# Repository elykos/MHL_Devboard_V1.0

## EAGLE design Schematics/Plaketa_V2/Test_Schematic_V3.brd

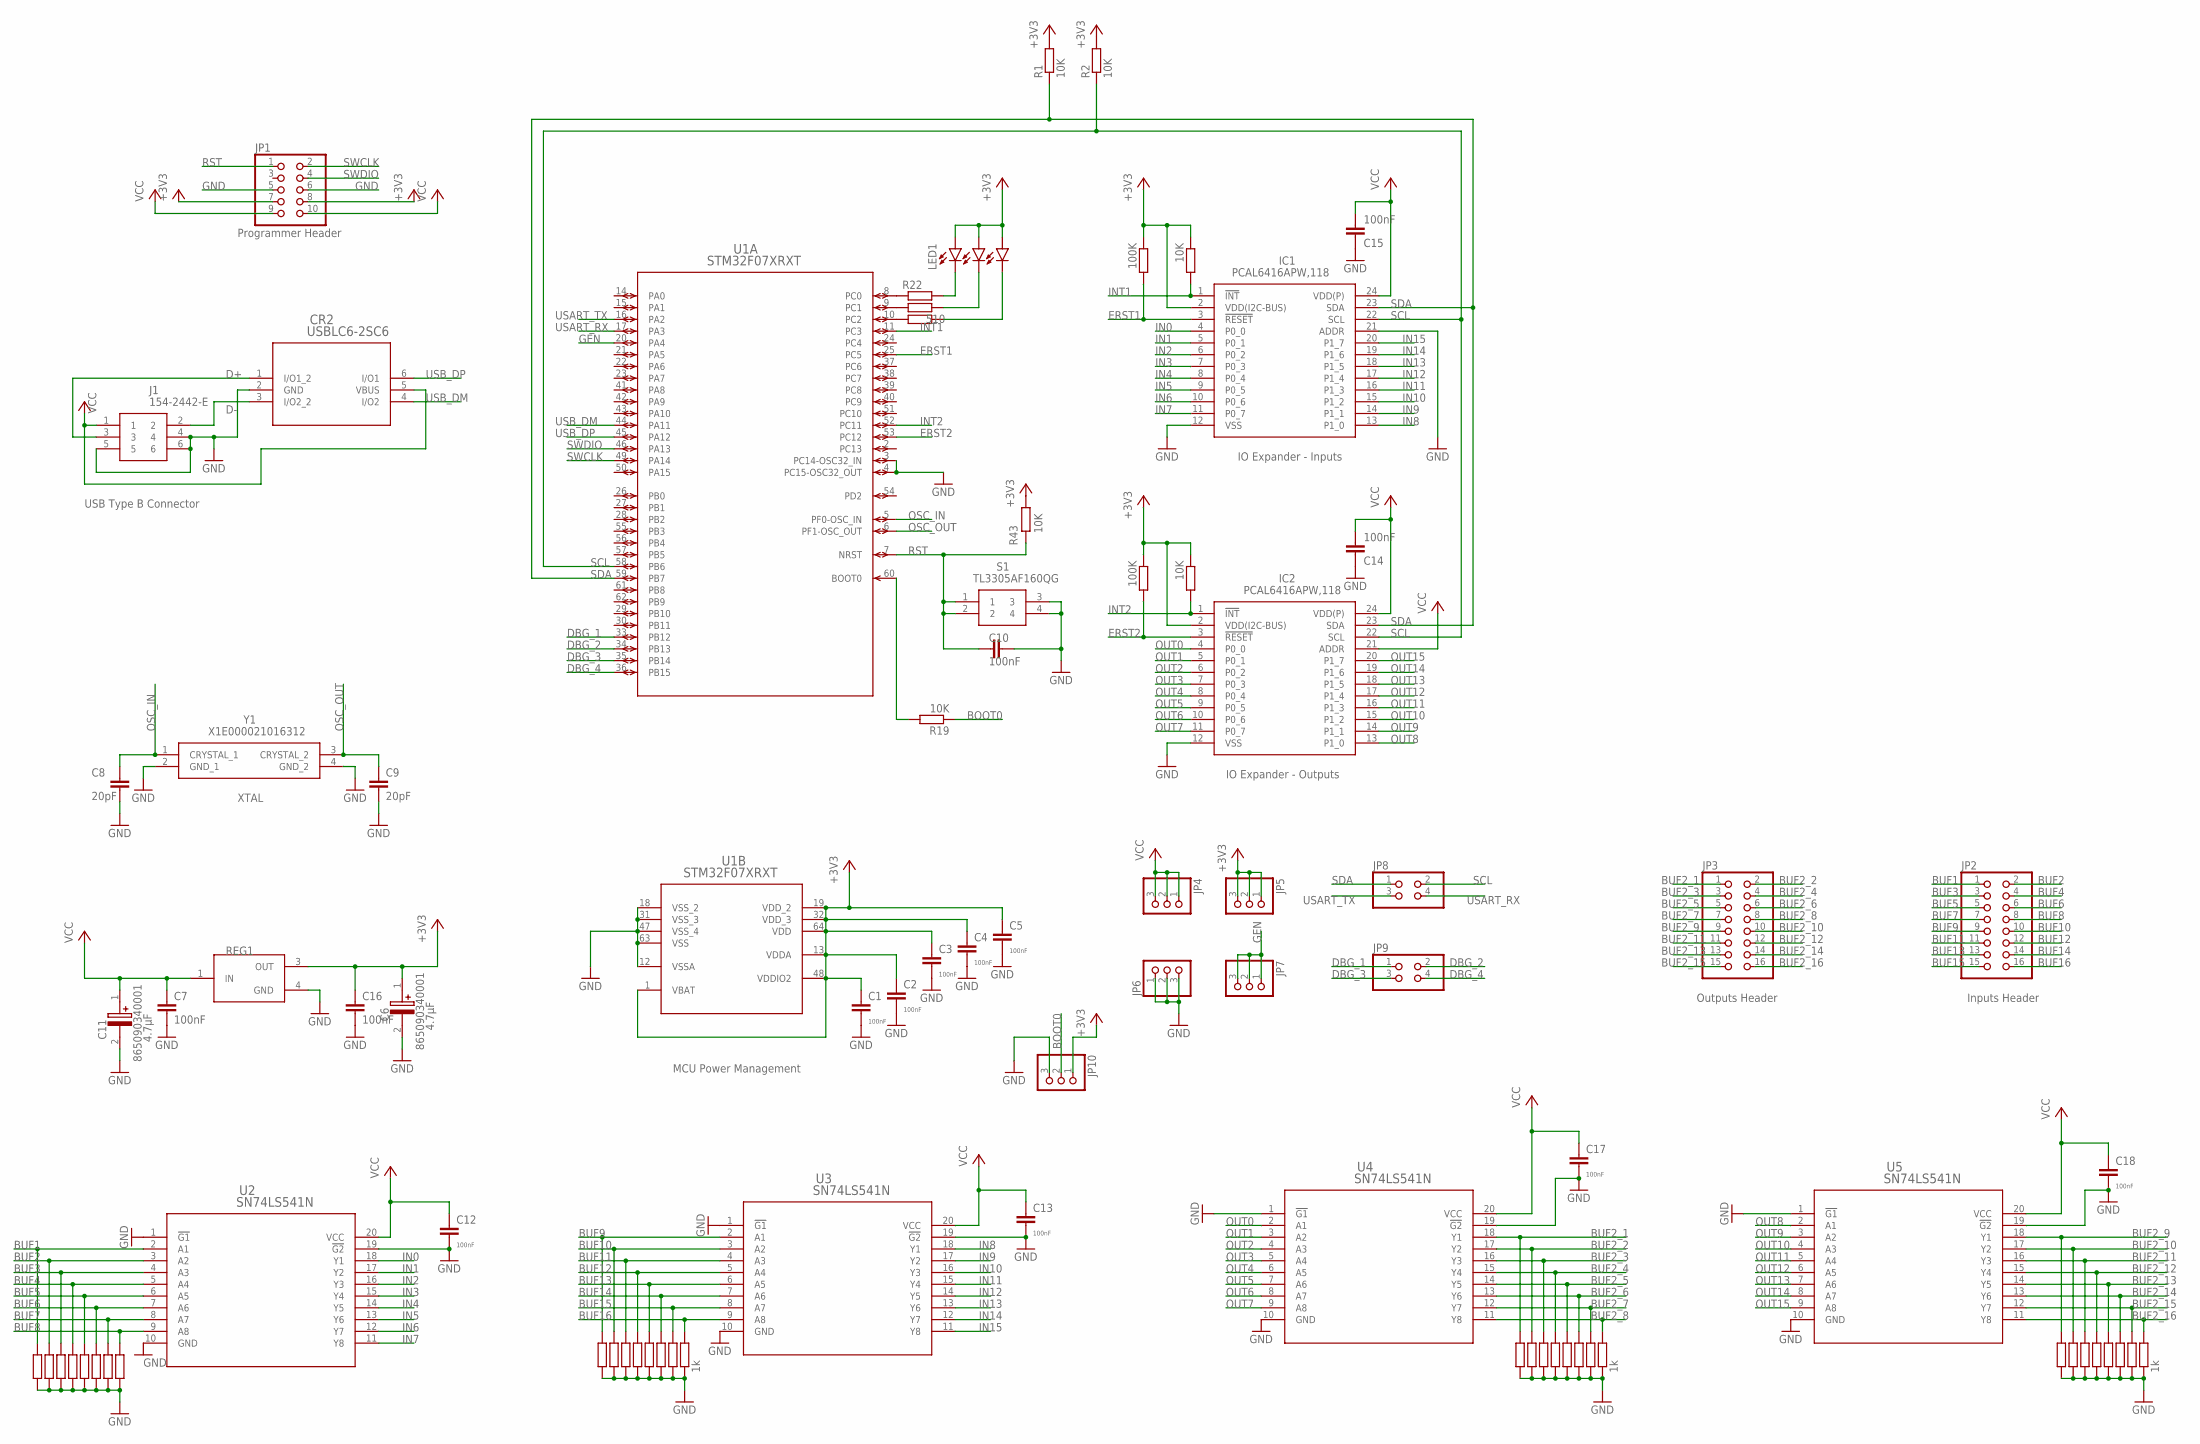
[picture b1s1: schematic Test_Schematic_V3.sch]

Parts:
C1, C2, C3, C4, C5, C7, C10, C12, C13, C14, C15, C16, C17, C18: 100nF; C1206
C6, C11: 865090340001; CAPAE430X550N
C8, C9: 20pF; C0805K
CR2: USBLC6-2SC6; SOT23-6L
IC1, IC2: PCAL6416APW,118; SOP65P640X110-24N
J1: 154-2442-E; 1542442E
JP1: PINHD-2X5; 2X05
JP2, JP3: PINHD-2X8; 2X08
JP4, JP5, JP6, JP7, JP10: PINHD-1X3; 1X03
JP8, JP9: PINHD-2X2; 2X02
LED1, LED2, LED3: LEDCHIP-LED0805; CHIP-LED0805
R1, R2, R19, R25, R26: 10K; R2010
R11, R12, R13, R14, R15, R16, R17, R22, R23, R28, R29, R30, R31, R32, R33, R34, R45, R46, R47, R48, R49, R50, R51, R53, R54, R55, R56, R57, R58, R59: R-EU_R0805; R0805
R18, R27, R44, R52: 1k; R0805
R20, R21: 100K; R2010
R24: 510; R0805
R43: 10K; R0805
REG1: LF33ABDT; DPAK
S1: TL3305AF160QG
U1: STM32F07XRXT; LQFP64-10X10MM
U2, U3, U4, U5: SN74LS541N; N20
Y1: X1E000021016312; TSX-3225_2

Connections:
+3V3: C1.1, C2.1, C3.1, C4.1, C5.1, C6.1 (+), C16.1, IC1.2 (VDD(I2C-BUS)), IC2.2 (VDD(I2C-BUS)), JP1.7, JP1.8, JP5.1, JP5.2, JP5.3, JP10.1, LED1.A, LED2.A, LED3.A, R1.2, R2.2, R20.1, R21.1, R25.1, R26.1, R43.1, REG1.3 (OUT), U1.1 (VBAT), U1.13 (VDDA), U1.19 (VDD_2), U1.32 (VDD_3), U1.48 (VDDIO2), U1.64 (VDD)
BOOT0: JP10.2, R19.1
BUF1: JP2.1, R11.2, U2.2 (A1)
BUF2: JP2.2, R12.2, U2.3 (A2)
BUF2_1: JP3.1, R51.2, U4.18 (Y1)
BUF2_2: JP3.2, R50.2, U4.17 (Y2)
BUF2_3: JP3.3, R49.2, U4.16 (Y3)
BUF2_4: JP3.4, R48.2, U4.15 (Y4)
BUF2_5: JP3.5, R47.2, U4.14 (Y5)
BUF2_6: JP3.6, R46.1, U4.13 (Y6)
BUF2_7: JP3.7, R45.2, U4.12 (Y7)
BUF2_8: JP3.8, R44.2, U4.11 (Y8)
BUF2_9: JP3.9, R59.2, U5.18 (Y1)
BUF2_10: JP3.10, R58.2, U5.17 (Y2)
BUF2_11: JP3.11, R57.2, U5.16 (Y3)
BUF2_12: JP3.12, R56.2, U5.15 (Y4)
BUF2_13: JP3.13, R55.2, U5.14 (Y5)
BUF2_14: JP3.14, R54.1, U5.13 (Y6)
BUF2_15: JP3.15, R53.2, U5.12 (Y7)
BUF2_16: JP3.16, R52.2, U5.11 (Y8)
BUF3: JP2.3, R13.2, U2.4 (A3)
BUF4: JP2.4, R14.2, U2.5 (A4)
BUF5: JP2.5, R15.2, U2.6 (A5)
BUF6: JP2.6, R16.2, U2.7 (A6)
BUF7: JP2.7, R17.2, U2.8 (A7)
BUF8: JP2.8, R18.2, U2.9 (A8)
BUF9: JP2.9, R34.2, U3.2 (A1)
BUF10: JP2.10, R33.2, U3.3 (A2)
BUF11: JP2.11, R32.2, U3.4 (A3)
BUF12: JP2.12, R31.2, U3.5 (A4)
BUF13: JP2.13, R30.2, U3.6 (A5)
BUF14: JP2.14, R29.1, U3.7 (A6)
BUF15: JP2.15, R28.2, U3.8 (A7)
BUF16: JP2.16, R27.2, U3.9 (A8)
D+: CR2.1 (I/O1_2), J1.3
D-: CR2.3 (I/O2_2), J1.2
DBG_1: JP9.1, U1.33 (PB12)
DBG_2: JP9.2, U1.34 (PB13)
DBG_3: JP9.3, U1.35 (PB14)
DBG_4: JP9.4, U1.36 (PB15)
ERST1: IC1.3 (!RESET), R20.2, U1.25 (PC5)
ERST2: IC2.3 (!RESET), R21.2, U1.53 (PC12)
GEN: JP7.1, JP7.2, JP7.3, U1.20 (PA4)
GND: C1.2, C2.2, C3.2, C4.2, C5.2, C6.2 (-), C7.2, C8.2, C9.2, C10.2, C11.2 (-), C12.2, C13.2, C14.1, C15.1, C16.2, C17.2, C18.2, CR2.2 (GND), IC1.12 (VSS), IC1.21 (ADDR), IC2.12 (VSS), J1.4, J1.5, J1.6, JP1.5, JP1.6, JP6.1, JP6.2, JP6.3, JP10.3, R11.1, R12.1, R13.1, R14.1, R15.1, R16.1, R17.1, R18.1, R27.1, R28.1, R29.2, R30.1, R31.1, R32.1, R33.1, R34.1, R44.1, R45.1, R46.2, R47.1, R48.1, R49.1, R50.1, R51.1, R52.1, R53.1, R54.2, R55.1, R56.1, R57.1, R58.1, R59.1, REG1.4 (GND), S1.3, S1.4, U1.3 (PC14-OSC32_IN), U1.4 (PC15-OSC32_OUT), U1.12 (VSSA), U1.18 (VSS_2), U1.31 (VSS_3), U1.47 (VSS_4), U1.63 (VSS), U2.1 (!G1), U2.10 (GND), U2.19 (!G2), U3.1 (!G1), U3.10 (GND), U3.19 (!G2), U4.1 (!G1), U4.10 (GND), U4.19 (!G2), U5.1 (!G1), U5.10 (GND), U5.19 (!G2), Y1.2 (GND_1), Y1.4 (GND_2)
IN0: IC1.4 (P0_0), U2.18 (Y1)
IN1: IC1.5 (P0_1), U2.17 (Y2)
IN2: IC1.6 (P0_2), U2.16 (Y3)
IN3: IC1.7 (P0_3), U2.15 (Y4)
IN4: IC1.8 (P0_4), U2.14 (Y5)
IN5: IC1.9 (P0_5), U2.13 (Y6)
IN6: IC1.10 (P0_6), U2.12 (Y7)
IN7: IC1.11 (P0_7), U2.11 (Y8)
IN8: IC1.13 (P1_0), U3.18 (Y1)
IN9: IC1.14 (P1_1), U3.17 (Y2)
IN10: IC1.15 (P1_2), U3.16 (Y3)
IN11: IC1.16 (P1_3), U3.15 (Y4)
IN12: IC1.17 (P1_4), U3.14 (Y5)
IN13: IC1.18 (P1_5), U3.13 (Y6)
IN14: IC1.19 (P1_6), U3.12 (Y7)
IN15: IC1.20 (P1_7), U3.11 (Y8)
INT1: IC1.1 (!INT), R26.2, U1.11 (PC3)
INT2: IC2.1 (!INT), R25.2, U1.52 (PC11)
unnamed: R22.1, U1.8 (PC0)
unnamed: R19.2, U1.60 (BOOT0)
unnamed: LED1.C, R22.2
unnamed: R23.1, U1.9 (PC1)
unnamed: LED2.C, R23.2
unnamed: LED3.C, R24.2
unnamed: R24.1, U1.10 (PC2)
OSC_IN: C8.1, U1.5 (PF0-OSC_IN), Y1.1 (CRYSTAL_1)
OSC_OUT: C9.1, U1.6 (PF1-OSC_OUT), Y1.3 (CRYSTAL_2)
OUT0: IC2.4 (P0_0), U4.2 (A1)
OUT1: IC2.5 (P0_1), U4.3 (A2)
OUT2: IC2.6 (P0_2), U4.4 (A3)
OUT3: IC2.7 (P0_3), U4.5 (A4)
OUT4: IC2.8 (P0_4), U4.6 (A5)
OUT5: IC2.9 (P0_5), U4.7 (A6)
OUT6: IC2.10 (P0_6), U4.8 (A7)
OUT7: IC2.11 (P0_7), U4.9 (A8)
OUT8: IC2.13 (P1_0), U5.2 (A1)
OUT9: IC2.14 (P1_1), U5.3 (A2)
OUT10: IC2.15 (P1_2), U5.4 (A3)
OUT11: IC2.16 (P1_3), U5.5 (A4)
OUT12: IC2.17 (P1_4), U5.6 (A5)
OUT13: IC2.18 (P1_5), U5.7 (A6)
OUT14: IC2.19 (P1_6), U5.8 (A7)
OUT15: IC2.20 (P1_7), U5.9 (A8)
RST: C10.1, JP1.1, R43.2, S1.1, S1.2, U1.7 (NRST)
SCL: IC1.22 (SCL), IC2.22 (SCL), JP8.2, R2.1, U1.58 (PB6)
SDA: IC1.23 (SDA), IC2.23 (SDA), JP8.1, R1.1, U1.59 (PB7)
SWCLK: JP1.2, U1.49 (PA14)
SWDIO: JP1.4, U1.46 (PA13)
USART_RX: JP8.4, U1.17 (PA3)
USART_TX: JP8.3, U1.16 (PA2)
USB_DM: CR2.4 (I/O2), U1.44 (PA11)
USB_DP: CR2.6 (I/O1), U1.45 (PA12)
VCC: C7.1, C11.1 (+), C12.1, C13.1, C14.2, C15.2, C17.1, C18.1, CR2.5 (VBUS), IC1.24 (VDD(P)), IC2.21 (ADDR), IC2.24 (VDD(P)), J1.1, JP1.9, JP1.10, JP4.1, JP4.2, JP4.3, REG1.1 (IN), U2.20 (VCC), U3.20 (VCC), U4.20 (VCC), U5.20 (VCC)

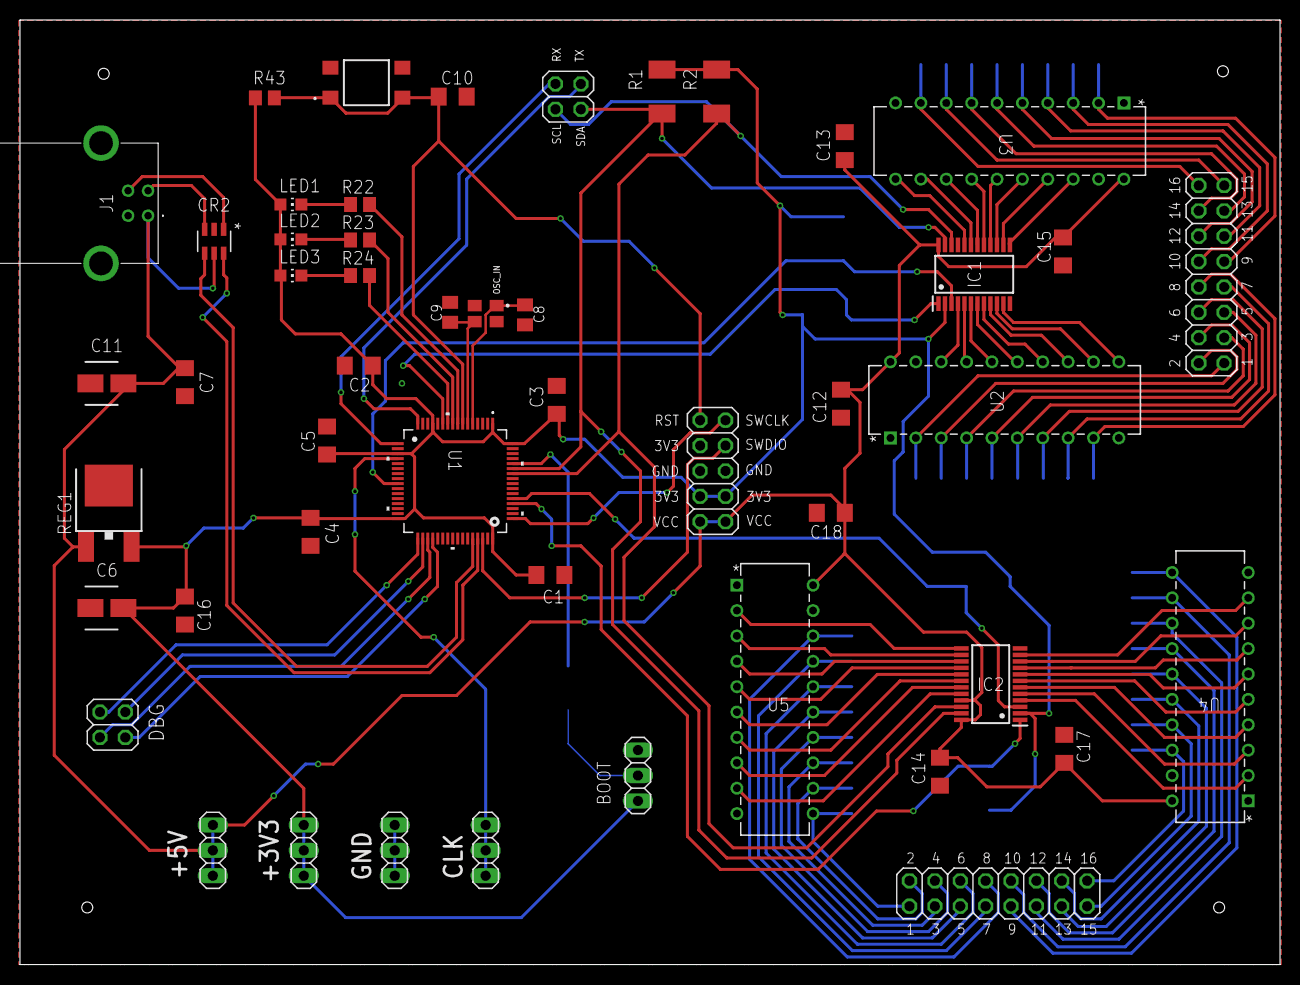
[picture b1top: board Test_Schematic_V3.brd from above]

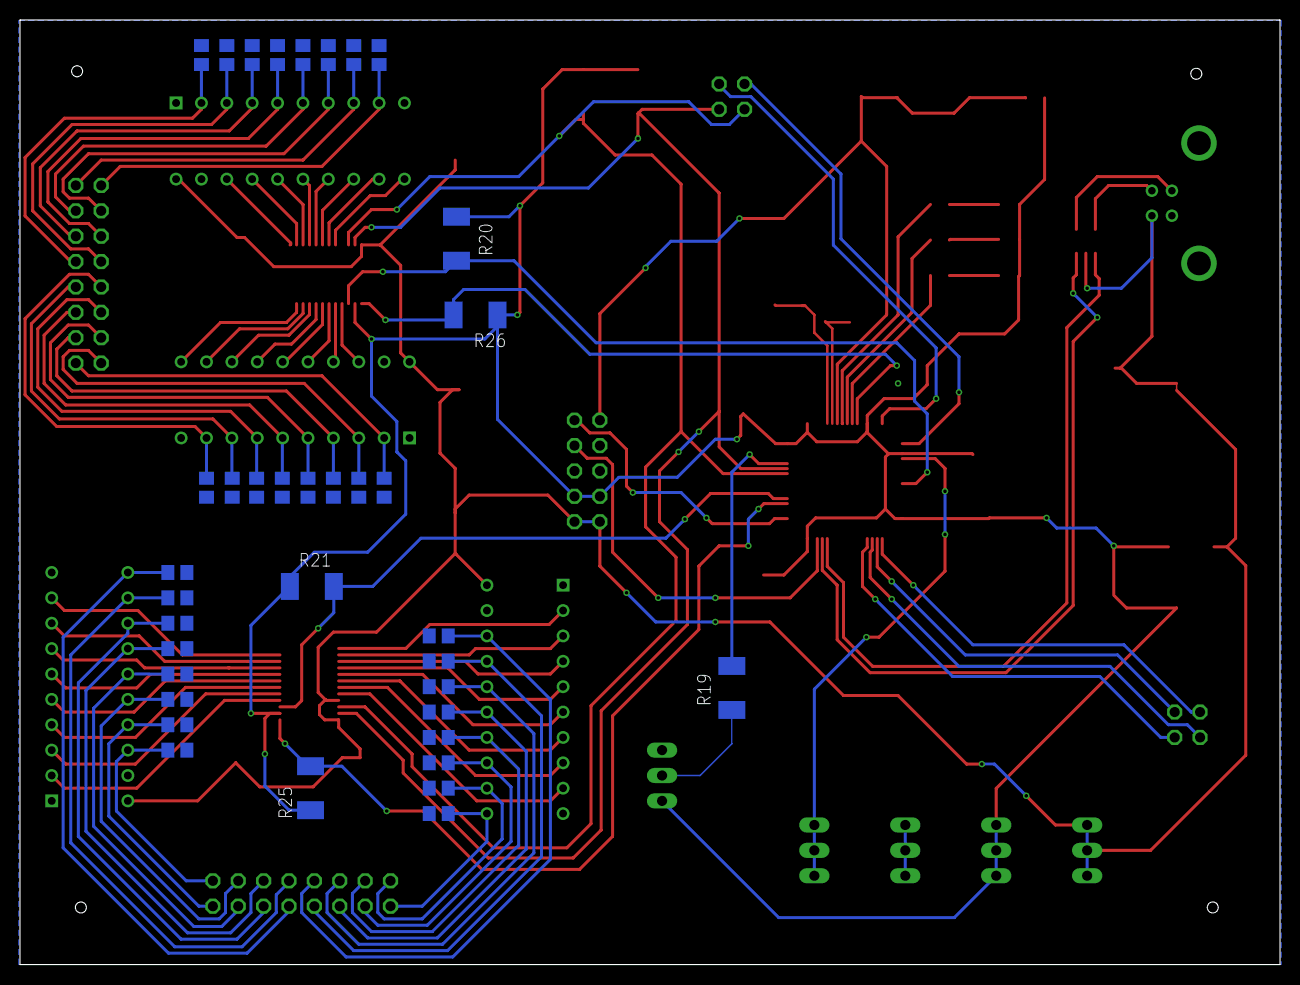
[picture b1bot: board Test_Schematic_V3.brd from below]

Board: 2 copper layers, 126.1 x 94.5 mm, 86 parts (37 on the bottom side), 97 nets.

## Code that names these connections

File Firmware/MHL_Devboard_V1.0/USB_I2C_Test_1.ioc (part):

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Mcu.Name=STM32F072R(8-B)Tx
Mcu.Package=LQFP64
Mcu.UserName=STM32F072RBTx
PA11.GPIOParameters=GPIO_Label
PA11.GPIO_Label=USBF4_DM
PA11.Mode=Device
PA11.Signal=USB_DM
PA12.GPIOParameters=GPIO_Label
PA12.GPIO_Label=USBF4_DP
PA12.Mode=Device
PA12.Signal=USB_DP
PA13.GPIOParameters=GPIO_Label
PA13.GPIO_Label=SWDIO
PA13.Mode=Serial_Wire
PA13.Signal=SYS_SWDIO
PA14.GPIOParameters=GPIO_Label
PA14.GPIO_Label=SWCLK
PA14.Mode=Serial_Wire
PA14.Signal=SYS_SWCLK
PA2.Mode=Asynchronous
PA2.Signal=USART2_TX
PA3.Mode=Asynchronous
PA3.Signal=USART2_RX
PA4.GPIOParameters=GPIO_Speed,GPIO_Label
PA4.GPIO_Label=GEN
PA4.GPIO_Speed=GPIO_SPEED_FREQ_HIGH
PA4.Signal=GPIO_Output
PB10.GPIOParameters=GPIO_Label
PB10.GPIO_Label=I2C2_SCL[EXT/RF-E2P_SCL]
PB10.Signal=I2C2_SCL
PB11.GPIOParameters=GPIO_Label
PB11.GPIO_Label=I2C2_SDA[EXT/RF-E2P_SDA]
PB11.Signal=I2C2_SDA
PB12.GPIOParameters=GPIO_Label
PB12.GPIO_Label=DBG_1
PB12.Signal=GPIO_Output
PB13.GPIOParameters=GPIO_Label
PB13.GPIO_Label=DBG_2
PB13.Signal=GPIO_Output
PB14.GPIOParameters=GPIO_Label
PB14.GPIO_Label=DBG_3
PB14.Signal=GPIO_Output
PB15.GPIOParameters=GPIO_Label
PB15.GPIO_Label=DBG_4
PB15.Signal=GPIO_Output
PB6.Mode=I2C
PB6.Signal=I2C1_SCL
PB7.Mode=I2C
PB7.Signal=I2C1_SDA
PC0.GPIOParameters=GPIO_Speed,PinState,GPIO_Label,GPIO_ModeDefaultOutputPP
PC0.GPIO_Label=LED1
PC0.GPIO_ModeDefaultOutputPP=GPIO_MODE_OUTPUT_OD
PC0.GPIO_Speed=GPIO_SPEED_FREQ_LOW
PC0.PinState=GPIO_PIN_SET
PC0.Signal=GPIO_Output
PC1.GPIOParameters=PinState,GPIO_Label,GPIO_ModeDefaultOutputPP
PC1.GPIO_Label=LED2
PC1.GPIO_ModeDefaultOutputPP=GPIO_MODE_OUTPUT_OD
PC1.PinState=GPIO_PIN_SET
PC1.Signal=GPIO_Output
PC11.GPIOParameters=GPIO_Label,GPIO_ModeDefaultEXTI
PC11.GPIO_Label=INT_2
PC11.GPIO_ModeDefaultEXTI=GPIO_MODE_IT_FALLING
PC11.Signal=GPXTI11
PC12.GPIOParameters=GPIO_Label,GPIO_ModeDefaultOutputPP
PC12.GPIO_Label=ERST_2
PC12.GPIO_ModeDefaultOutputPP=GPIO_MODE_OUTPUT_OD
PC12.Signal=GPIO_Output
PC2.GPIOParameters=PinState,GPIO_Label,GPIO_ModeDefaultOutputPP
PC2.GPIO_Label=LED3
PC2.GPIO_ModeDefaultOutputPP=GPIO_MODE_OUTPUT_OD
PC2.PinState=GPIO_PIN_SET
PC2.Signal=GPIO_Output
PC3.GPIOParameters=GPIO_Label,GPIO_ModeDefaultEXTI
PC3.GPIO_Label=INT_1
PC3.GPIO_ModeDefaultEXTI=GPIO_MODE_IT_FALLING
PC3.Signal=GPXTI3
PC5.GPIOParameters=GPIO_Label,GPIO_ModeDefaultOutputPP
PC5.GPIO_Label=ERST_1
PC5.GPIO_ModeDefaultOutputPP=GPIO_MODE_OUTPUT_OD
PC5.Signal=GPIO_Output
PF0-OSC_IN.Mode=HSE-External-Clock-Source
PF0-OSC_IN.Signal=RCC_OSC_IN
RCC.SYSCLKFreq_VALUE=48000000
RCC.SYSCLKSource=RCC_SYSCLKSOURCE_PLLCLK
board=STM32F072B-DISCO
boardIOC=true

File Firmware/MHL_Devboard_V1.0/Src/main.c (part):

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			  else if(data_buffer[1] == encoded_command_byte_2[3])
			  {
				  /* Start the countdown timer */
				  HAL_GPIO_WritePin(GEN_GPIO_Port, GEN_Pin, GPIO_PIN_SET);
				  HAL_TIM_Base_Start(&htim6);
			  }

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  HAL_GPIO_WritePin(GPIOC, LED1_Pin|LED2_Pin|LED3_Pin, GPIO_PIN_SET);

  /*Configure GPIO pin Output Level */
  HAL_GPIO_WritePin(GEN_GPIO_Port, GEN_Pin, GPIO_PIN_RESET);

  /*Configure GPIO pin Output Level */
  HAL_GPIO_WritePin(GPIOC, ERST_1_Pin|ERST_2_Pin, GPIO_PIN_RESET);

  /*Configure GPIO pin Output Level */
  HAL_GPIO_WritePin(GPIOB, DBG_1_Pin|DBG_2_Pin|DBG_3_Pin|DBG_4_Pin, GPIO_PIN_RESET);

  /*Configure GPIO pins : PC13 PC14 PC15 PC4 
                           PC6 PC7 PC8 PC9 
                           PC10 */
  GPIO_InitStruct.Pin = GPIO_PIN_13|GPIO_PIN_14|GPIO_PIN_15|GPIO_PIN_4 
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  GPIO_InitStruct.Pull = GPIO_NOPULL;
  HAL_GPIO_Init(GPIOC, &GPIO_InitStruct);

  /*Configure GPIO pin : PF1 */
  GPIO_InitStruct.Pin = GPIO_PIN_1;
  GPIO_InitStruct.Mode = GPIO_MODE_ANALOG;
  GPIO_InitStruct.Pull = GPIO_NOPULL;
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  GPIO_InitStruct.Pull = GPIO_NOPULL;
  HAL_GPIO_Init(GPIOA, &GPIO_InitStruct);

  /*Configure GPIO pin : GEN_Pin */
  GPIO_InitStruct.Pin = GEN_Pin;
  GPIO_InitStruct.Mode = GPIO_MODE_OUTPUT_PP;
  GPIO_InitStruct.Pull = GPIO_NOPULL;
  GPIO_InitStruct.Speed = GPIO_SPEED_FREQ_HIGH;
  HAL_GPIO_Init(GEN_GPIO_Port, &GPIO_InitStruct);

  /*Configure GPIO pins : PB0 PB1 PB2 PB3 
                           PB4 PB5 PB8 PB9 */
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  GPIO_InitStruct.Alternate = GPIO_AF1_I2C2;
  HAL_GPIO_Init(GPIOB, &GPIO_InitStruct);

  /*Configure GPIO pins : DBG_1_Pin DBG_2_Pin DBG_3_Pin DBG_4_Pin */
  GPIO_InitStruct.Pin = DBG_1_Pin|DBG_2_Pin|DBG_3_Pin|DBG_4_Pin;
  GPIO_InitStruct.Mode = GPIO_MODE_OUTPUT_PP;
  GPIO_InitStruct.Pull = GPIO_NOPULL;
  GPIO_InitStruct.Speed = GPIO_SPEED_FREQ_LOW;
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	if(htim->Instance == TIM6)
	{
		HAL_TIM_Base_Stop(&htim6);
		HAL_GPIO_WritePin(GEN_GPIO_Port, GEN_Pin, GPIO_PIN_RESET);
	}

	// Set the flag to transmit inputs status
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
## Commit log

2020-07-24 Added Project Files
2020-07-24 Upload EAGLE Schematics
2020-08-26 Upload GUI
    MHL Development Board Control resize fixes
2020-08-27 Upload ZIP with installation executable

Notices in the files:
Firmware/MHL_Devboard_V1.0/Src/main.c:
© Copyright (c) 2019 STMicroelectronics.
All rights reserved.
This software component is licensed by ST under BSD 3-Clause license,
the "License"; You may not use this file except in compliance with the
License. You may obtain a copy of the License at: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
(C) COPYRIGHT STMicroelectronics *****END OF FILE
